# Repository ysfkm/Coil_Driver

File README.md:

# Coil Driver

## Summary
- Board hosting three independent bi-directional coil drivers (up to 3A each) off a shared +15V supply, using an H-bridge per channel for direction control.
- Setpoints for each channel's analog current control loop are set digitally over a backplane bus (address + data bits → DAC → analog loop); 4-layer 163mm x 100mm PCB.

## Specs
- **Input:** Digital Bus from backplane
  - A0~A7 as addresses
  - D9~D14 as data bits
- **Supply:** An external +15V with 10A rating and +15V from backplane
- **Output:** three bi-directional current up to 3A
- **Description:** Three separate coil drivers each capable of outputting 3A using the same +15V supply to output current. Utilizes digital interface from the backplane to set the setpoints for the analog current control loops separately and uses H-bridge to achieve bi-directional capability.
- **PCB:** 163mm x 100mm / 4 Layer

> **⚠ Note:** When setting a setpoint via the SPI lines, make sure the DIR bits are all driven to the right value since all DIR bits would be updated at the same time, not just the targeted channel for setpoint adjustment.

> **⚠ Note:** For the jumper selecting +15V power supply, make sure either ALL FOUR middle pins are connected or the LEFT AND RIGHT pins are connected, NEVER BOTH.

## Voltage / Nets

| Voltage / Nets | Purpose |
|---|---|
| +15V_EXT | External supply for driving large currents |
| +15V_BP | Backplane supply for regulating voltages and driving small currents |
| +15V | Jumper implemented to choose between +15V_EXT and +15V_BP<br>Drives main op-amp for current output<br>Drives MOSFETs to control H-bridge switching |
| +6V | Regulated from +15_BP, used to regulate +5VA |
| +5VA | Drives DAC and sensing op-amp. Used to generate VREF for DAC |
| +5V | Backplane supply to regulate +3V3 |
| +3V3 | Backplane supply for digital decoder |
| +3V3A | Regulated from +15V_BP, drives DAC |

## Modules

### Root page
- Backplane connector with digital bus, supply, and ground
- This board's own address switch
- Digital decoder latching the data bits when address from A0~A7 matches

### Power Supply page
- Several ferrite beads to connect different ground domains

### DAC
- Takes the three SPI lines and output 0~3V setpoint
- Has four channels, three used for each analog control loop
- Own regulator to precisely generate reference voltage (3V)

### Analog Control pages
All three are basically identical and have the following:
- Main op-amp driving the current
- Setpoint at main op-amp
- Compensator at main op-amp
- Current sense feedback network and voltage amplifier
- H-bridge
- MOSFET gate driver that drives the H-bridge based on DIR bit

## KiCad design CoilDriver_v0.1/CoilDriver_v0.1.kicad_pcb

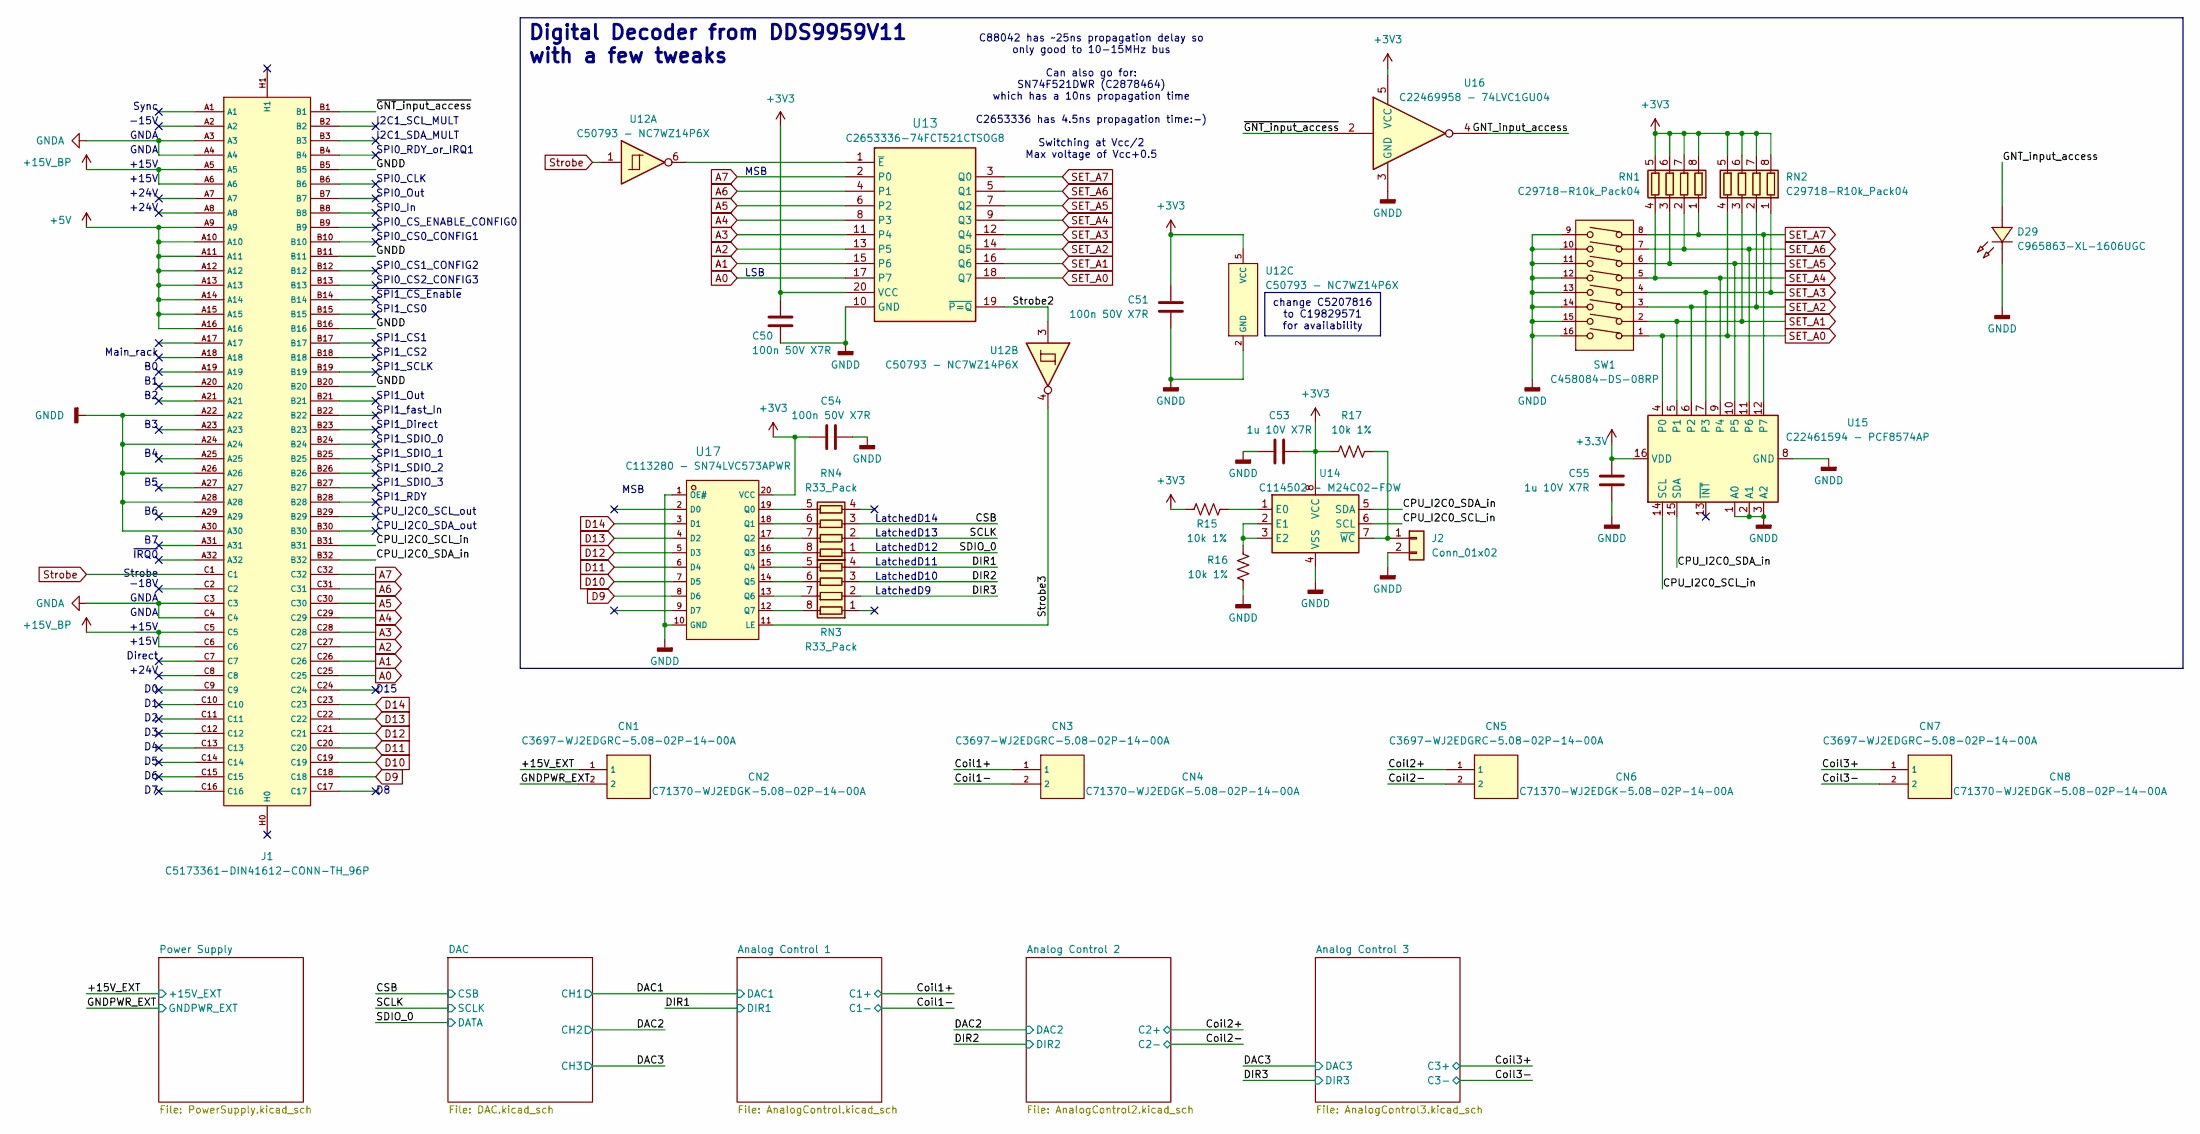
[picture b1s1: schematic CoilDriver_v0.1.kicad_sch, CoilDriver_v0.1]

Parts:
C50, C51, C54: 100n 50V X7R; C_0402_1005Metric; LCSC C307331
C53, C55: 1u 10V X7R; C_0402_1005Metric; LCSC C7500381
CN1, CN3, CN5, CN7: C3697-WJ2EDGRC-5.08-02P-14-00A; C3697-CONN-TH_2P-P5.08_WJ2EDGRC-5.08-2P; LCSC C3697
CN2, CN4, CN6, CN8: C71370-WJ2EDGK-5.08-02P-14-00A; C71370-FL_001; LCSC C71370
D29: C965863-XL-1606UGC; C965863-LED-SMD_L1.7-W1.1-R-RD_ORANGE; LCSC C965863
J1: C5173361-DIN41612-CONN-TH_96P; C5173361-DIN41612-96P; LCSC C5173361
J2: Conn_01x02; C492401-HDR-TH_2P-P2.54-V-M; LCSC C492401
R15, R16, R17: 10k 1%; R_0402_1005Metric; LCSC C2906861
RN1, RN2: C29718-R10k_Pack04; C29718-RES-ARRAY-SMD_0603-8P-L3.2-W1.6-BL; LCSC C29718
RN3, RN4: R33_Pack; C25508-RES-ARRAY-SMD_0603-8P-L3.2-W1.6-BL; LCSC C25508
SW1: C458084-DS-08RP; C458084-SW-TH_DS-08RP; LCSC C458084
U12: C50793 - NC7WZ14P6X; C50793-SC-70-6_L2.2-W1.3-P0.65-LS2.2-BR; LCSC C50793
U13: C2653336-74FCT521CTSOG8; C2653336-SOIC127P1032X265-20N; LCSC C2653336
U14: C114502 - M24C02-FDW; C114502-SOIC-8_L4.9-W3.9-P1.27-LS6.0-BL; LCSC C114502
U15: C22461594 - PCF8574AP; C22461594-TSSOP-16_L5.0-W4.4-P0.65-LS6.4-BL-1; LCSC C22461594
U16: C22469958 - 74LVC1GU04; C22469958-SOT-353-5_L2.1-W1.3-P0.65-LS2.3-BL; LCSC C22469958
U17: C113280 - SN74LVC573APWR; C113280-TSSOP-20_L6.5-W4.4-P0.65-LS6.4-BL; LCSC C113280

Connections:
+3.3V: C55.1, U15.16 (VDD)
+3V3: C50.1, C51.1, C53.1, C54.1, R15.1, R17.1, RN1.5 (R4.2), RN1.6 (R3.2), RN1.7 (R2.2), RN1.8 (R1.2), RN2.5 (R4.2), RN2.6 (R3.2), RN2.7 (R2.2), RN2.8 (R1.2), U12.5 (VCC), U13.20 (VCC), U14.8 (VCC), U16.5 (VCC), U17.20 (VCC); also elsewhere on the board
+5V: J1.A9, J1.A10, J1.A11, J1.A12, J1.A13, J1.A14, J1.A15, J1.A16; also elsewhere on the board
+15V_BP: J1.A5, J1.A6, J1.C5, J1.C6; also elsewhere on the board
/+15V_EXT: CN1.1; also elsewhere on the board
/CPU_I2C0_SCL_in: J1.B31, U14.6 (SCL), U15.14 (SCL)
/CPU_I2C0_SDA_in: J1.B32, U14.5 (SDA), U15.15 (SDA)
/CSB: RN4.3 (R3.1); also elsewhere on the board
/Coil1+: CN3.1; also elsewhere on the board
/Coil1-: CN3.2; also elsewhere on the board
/Coil2+: CN5.1; also elsewhere on the board
/Coil2-: CN5.2; also elsewhere on the board
/Coil3+: CN7.1; also elsewhere on the board
/Coil3-: CN7.2; also elsewhere on the board
/DIR1: RN3.4 (R4.1); also elsewhere on the board
/DIR2: RN3.3 (R3.1); also elsewhere on the board
/DIR3: RN3.2 (R2.1); also elsewhere on the board
/GNT_input_access: D29.2 (A), U16.4
/SCLK: RN4.2 (R2.1); also elsewhere on the board
/SDIO_0: RN4.1 (R1.1); also elsewhere on the board
/Strobe2: U12.3, U13.19 (~P=Q)
/Strobe3: U12.4, U17.11 (LE)
/~GNT_input_access: J1.B1, U16.2
A0: J1.C25, U13.17 (P7)
A1: J1.C26, U13.15 (P6)
A2: J1.C27, U13.13 (P5)
A3: J1.C28, U13.11 (P4)
A4: J1.C29, U13.8 (P3)
A5: J1.C30, U13.6 (P2)
A6: J1.C31, U13.4 (P1)
A7: J1.C32, U13.2 (P0)
D9: J1.C18, U17.8 (D6)
D10: J1.C19, U17.7 (D5)
D11: J1.C20, U17.6 (D4)
D12: J1.C21, U17.5 (D3)
D13: J1.C22, U17.4 (D2)
D14: J1.C23, U17.3 (D1)
GNDA: J1.A3, J1.A4, J1.C3, J1.C4; also elsewhere on the board
GNDD: C50.2, C51.2, C53.2, C54.2, C55.2, D29.1 (K), J1.A22, J1.A24, J1.A26, J1.A28, J1.A30, J1.B5, J1.B11, J1.B16, J1.B20, J2.2, R16.2, SW1.9, SW1.10, SW1.11, SW1.12, SW1.13, SW1.14, SW1.15, SW1.16, U12.2 (GND), U13.10 (GND), U14.4 (VSS), U15.1 (A0), U15.2 (A1), U15.3 (A2), U15.8 (GND), U16.3 (GND), U17.1 (OE#), U17.10 (GND); also elsewhere on the board
GNDPWR: CN1.2; also elsewhere on the board
unnamed: J2.1, R17.2, U14.7 (~WC)
unnamed: RN3.8 (R1.2), U17.12 (Q7)
unnamed: RN3.7 (R2.2), U17.13 (Q6)
unnamed: RN3.6 (R3.2), U17.14 (Q5)
unnamed: RN3.5 (R4.2), U17.15 (Q4)
unnamed: RN4.8 (R1.2), U17.16 (Q3)
unnamed: RN4.7 (R2.2), U17.17 (Q2)
unnamed: RN4.6 (R3.2), U17.18 (Q1)
unnamed: RN4.5 (R4.2), U17.19 (Q0)
unnamed: U12.6, U13.1 (~E)
unnamed: R15.2, U14.1 (E0)
unnamed: R16.1, U14.2 (E1), U14.3 (E2)
SET_A0: RN2.4 (R4.1), SW1.1, U13.18 (Q7), U15.4 (P0)
SET_A1: RN2.3 (R3.1), SW1.2, U13.16 (Q6), U15.5 (P1)
SET_A2: RN2.2 (R2.1), SW1.3, U13.14 (Q5), U15.6 (P2)
SET_A3: RN2.1 (R1.1), SW1.4, U13.12 (Q4), U15.7 (P3)
SET_A4: RN1.4 (R4.1), SW1.5, U13.9 (Q3), U15.9 (P4)
SET_A5: RN1.3 (R3.1), SW1.6, U13.7 (Q2), U15.10 (P5)
SET_A6: RN1.2 (R2.1), SW1.7, U13.5 (Q1), U15.11 (P6)
SET_A7: RN1.1 (R1.1), SW1.8, U13.3 (Q0), U15.12 (P7)
Strobe: J1.C1, U12.1

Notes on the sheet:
Main_rack
CPU_I2C0_SCL_out
SPI1_Direct
SPI0_CS2_CONFIG3
+24V
SPI0_CS_ENABLE_CONFIG0
+15V
SPI0_In
LatchedD14
Strobe
SPI1_CS1
SPI1_SCLK
SPI1_SDIO_2
SPI1_SDIO_3
SPI1_Out
Direct
GNDA
-18V
SPI1_SDIO_1
LatchedD11
CPU_I2C0_SDA_out
MSB
Sync
~{IRQ0}
LatchedD9
SPI0_CLK
D15
SPI0_Out
LSB
LatchedD10
SPI0_CS1_CONFIG2
SPI1_CS0
LatchedD13
SPI1_CS2
~{SPI1_CS_Enable}
SPI0_RDY_or_IRQ1
C88042 has ~25ns propagation delay so only good to 10-15MHz bus Can also go for: SN74F521DWR (C2878464) which has a 10ns propagation time C2653336 has 4.5ns propagation time:-) Switching at Vcc/2 Max voltage of Vcc+0.5
I2C1_SCL_MULT
I2C1_SDA_MULT
SPI1_SDIO_0

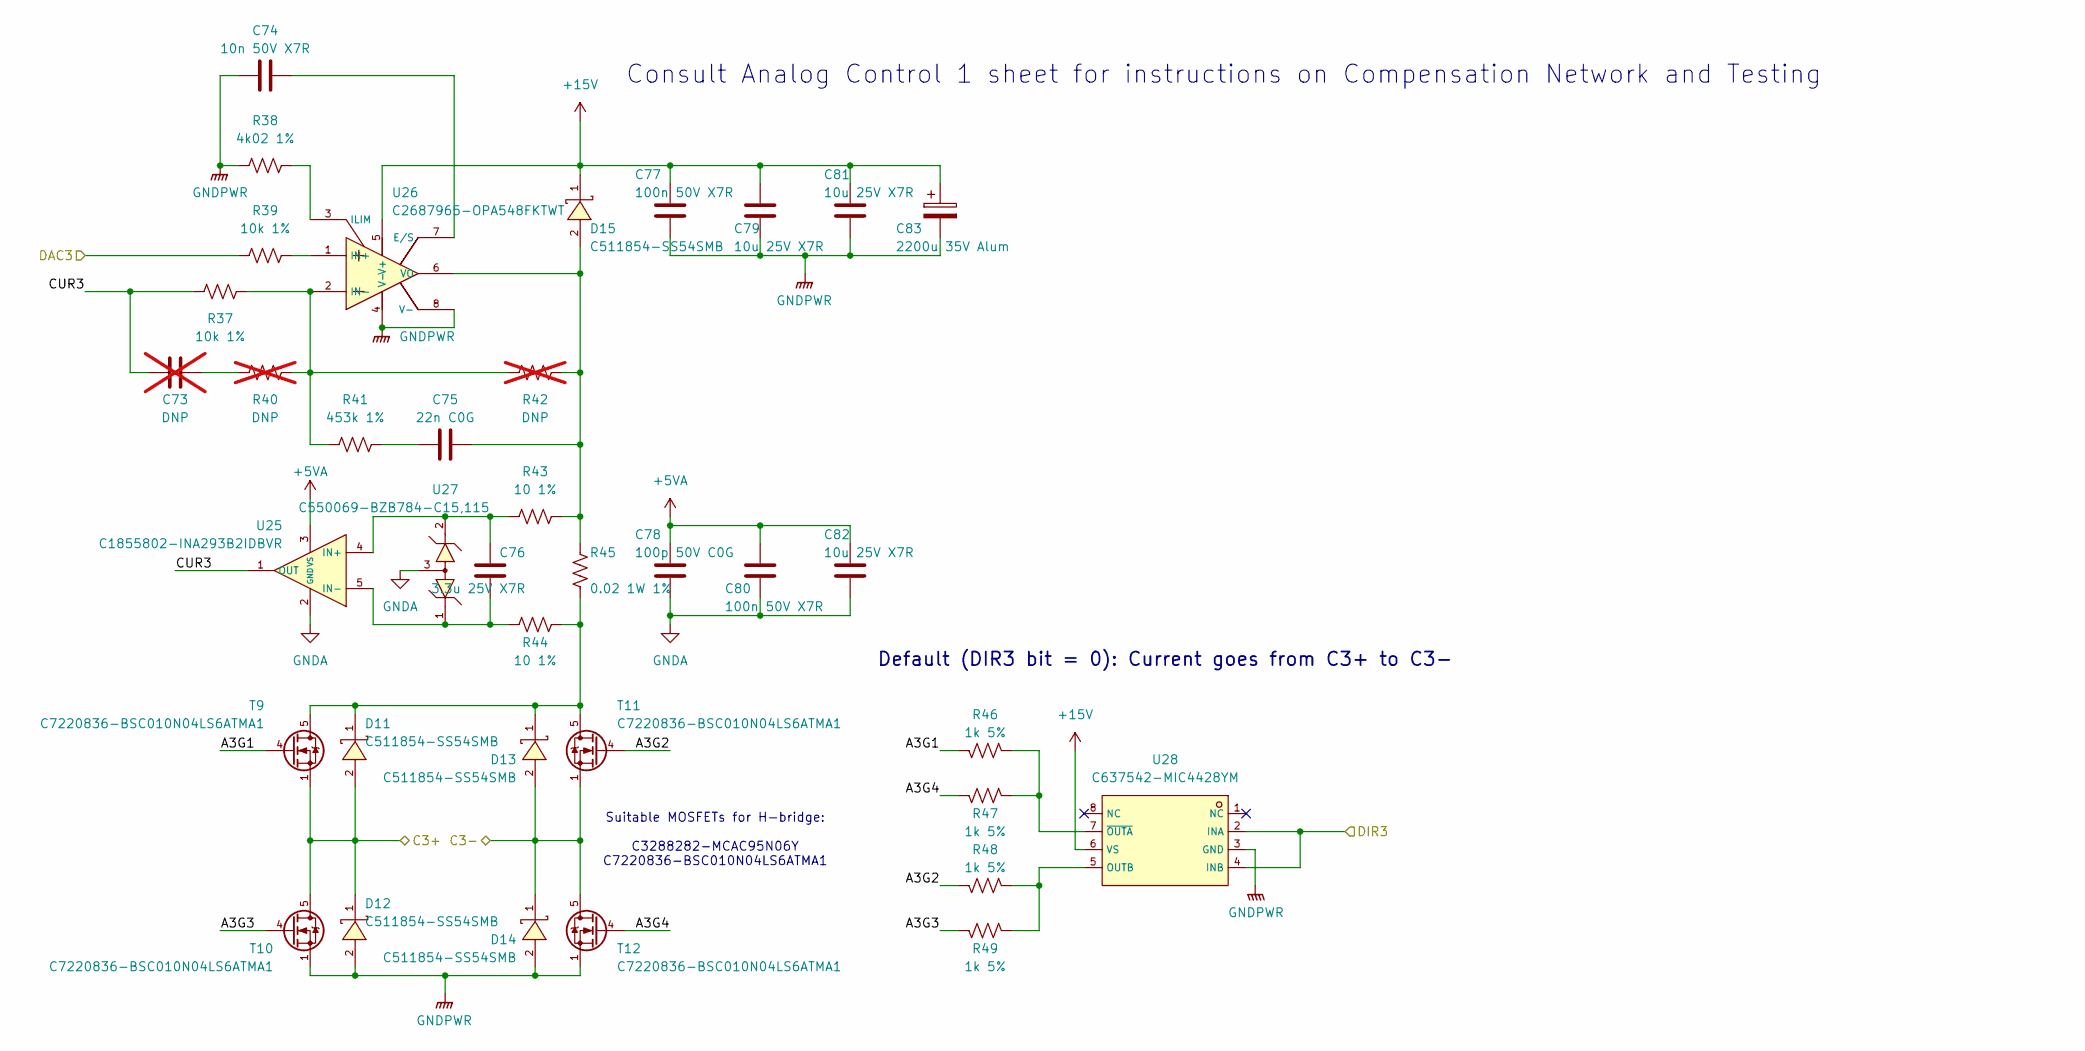
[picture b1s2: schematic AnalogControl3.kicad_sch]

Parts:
C73: DNP; C_0805_2012Metric; not fitted
C74: 10n 50V X7R; C_0402_1005Metric; LCSC C15195
C75: 22n C0G; C_0805_2012Metric; LCSC C2181592
C76: 3.3u 25V X7R; C_0805_2012Metric; LCSC C7393948
C77, C80: 100n 50V X7R; C_0402_1005Metric; LCSC C307331
C78: 100p 50V C0G; C_0402_1005Metric; LCSC C1546
C79, C81, C82: 10u 25V X7R; C_0805_2012Metric; LCSC C3039694
C83: 2200u 35V Alum; C3829879-CAP-SMD_BD16.0-L17.0-W17.0-LS18.0-FD; LCSC C3829879
D11, D12, D13, D14, D15: C511854-SS54SMB; C511854-SMB_L4.6-W3.6-LS5.3-RD; LCSC C511854
R37, R39: 10k 1%; R_0402_1005Metric; LCSC C2906861
R38: 4k02 1%; R_0402_1005Metric; LCSC C324800
R40, R42: DNP; R_0603_1608Metric; not fitted
R41: 453k 1%; R_0402_1005Metric; LCSC C3013172
R43, R44: 10 1%; R_0402_1005Metric; LCSC C138066
R45: 0.02 1W 1%; R_1206_3216Metric; LCSC C7420010
R46, R47, R48, R49: 1k 5%; R_0402_1005Metric; LCSC C2906899
T9, T10, T11, T12: C7220836-BSC010N04LS6ATMA1; C7220836-TDSON-8_L6.0-W5.0-P1.27-LS6.2-BL_1; LCSC C7220836
U25: C1855802-INA293B2IDBVR; C1855802-SOT-23-5_L2.9-W1.6-P0.95-LS2.8-BR; LCSC C1855802
U26: C2687965-OPA548FKTWT; C2687965-TO-263-7_L10.2-W8.9-P1.27-LS15.2-BL; LCSC C2687965
U27: C550069-BZB784-C15,115; C550069-SOT-323-3_L2.0-W1.3-P1.30-LS2.1-BR; LCSC C550069
U28: C637542-MIC4428YM; C637542-SOIC-8_L4.9-W3.9-P1.27-LS6.0-BL; LCSC C637542

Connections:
+5VA: C78.1, C80.1, C82.1, U25.3 (VS); also elsewhere on the board
+15V: C77.1, C79.1, C81.1, C83.1, D15.1 (K), U26.5 (V+), U28.6 (VS); also elsewhere on the board
/Analog Control 3/A3G1: R46.2, T9.4 (G)
/Analog Control 3/A3G2: R48.2, T11.4 (G)
/Analog Control 3/A3G3: R49.2, T10.4 (G)
/Analog Control 3/A3G4: R47.2, T12.4 (G)
/Analog Control 3/CUR3: C73.1, R37.1, U25.1 (OUT)
/Coil3+: D11.2 (A), D12.1 (K), T9.1 (S), T10.5 (D); also elsewhere on the board
/Coil3-: D13.2 (A), D14.1 (K), T11.1 (S), T12.5 (D); also elsewhere on the board
/DAC3: R39.1; also elsewhere on the board
/DIR3: U28.2 (INA), U28.4 (INB); also elsewhere on the board
GNDA: C78.2, C80.2, C82.2, U25.2 (GND), U27.3; also elsewhere on the board
GNDPWR: C74.1, C77.2, C79.2, C81.2, C83.2, D12.2 (A), D14.2 (A), R38.1, T10.1 (S), T12.1 (S), U26.4 (V-), U26.8 (V-), U28.3 (GND); also elsewhere on the board
unnamed: C73.2, R40.1
unnamed: C75.1, R41.2
unnamed: D11.1 (K), D13.1 (K), R44.1, R45.1, T9.5 (D), T11.5 (D)
unnamed: C75.2, D15.2 (A), R42.2, R43.1, R45.2, U26.6 (VO)
unnamed: C76.2, R43.2, U25.4 (IN+), U27.2
unnamed: C76.1, R44.2, U25.5 (IN-), U27.1
unnamed: C74.2, U26.7 (E/S)
unnamed: R38.2, U26.3 (ILIM)
unnamed: R39.2, U26.1 (IN+)
unnamed: R37.2, R40.2, R41.1, R42.1, U26.2 (IN-)
unnamed: R48.1, R49.1, U28.5 (OUTB)
unnamed: R46.1, R47.1, U28.7 (~OUTA)

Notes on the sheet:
Consult Analog Control 1 sheet for instructions on Compensation Network and Testing
Default (DIR3 bit = 0): Current goes from C3+ to C3-
Suitable MOSFETs for H-bridge: C3288282-MCAC95N06Y C7220836-BSC010N04LS6ATMA1

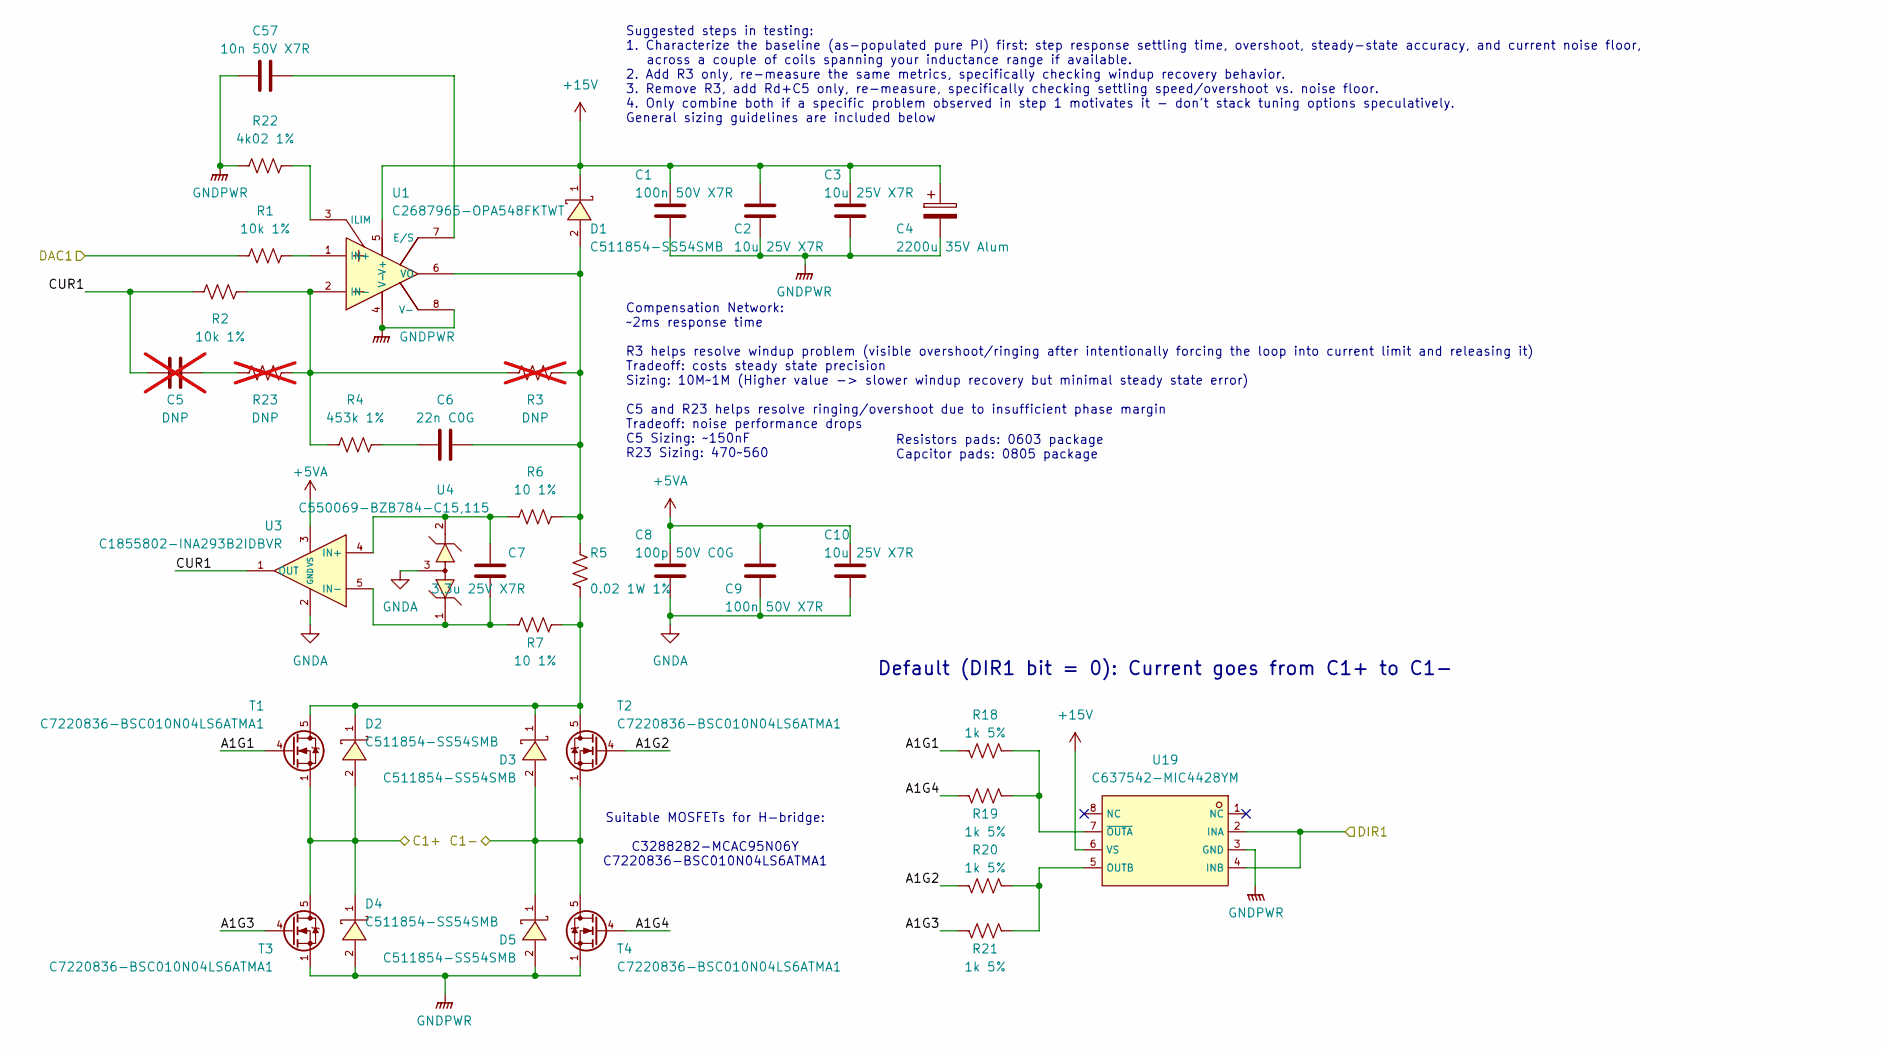
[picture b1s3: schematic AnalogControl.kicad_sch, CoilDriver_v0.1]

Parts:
C1, C9: 100n 50V X7R; C_0402_1005Metric; LCSC C307331
C2, C3, C10: 10u 25V X7R; C_0805_2012Metric; LCSC C3039694
C4: 2200u 35V Alum; C3829879-CAP-SMD_BD16.0-L17.0-W17.0-LS18.0-FD; LCSC C3829879
C5: DNP; C_0805_2012Metric; not fitted
C6: 22n C0G; C_0805_2012Metric; LCSC C2181592
C7: 3.3u 25V X7R; C_0805_2012Metric; LCSC C7393948
C8: 100p 50V C0G; C_0402_1005Metric; LCSC C1546
C57: 10n 50V X7R; C_0402_1005Metric; LCSC C15195
D1, D2, D3, D4, D5: C511854-SS54SMB; C511854-SMB_L4.6-W3.6-LS5.3-RD; LCSC C511854
R1, R2: 10k 1%; R_0402_1005Metric; LCSC C2906861
R3, R23: DNP; R_0603_1608Metric; not fitted
R4: 453k 1%; R_0402_1005Metric; LCSC C3013172
R5: 0.02 1W 1%; R_1206_3216Metric; LCSC C7420010
R6, R7: 10 1%; R_0402_1005Metric; LCSC C138066
R18, R19, R20, R21: 1k 5%; R_0402_1005Metric; LCSC C2906899
R22: 4k02 1%; R_0402_1005Metric; LCSC C324800
T1, T2, T3, T4: C7220836-BSC010N04LS6ATMA1; C7220836-TDSON-8_L6.0-W5.0-P1.27-LS6.2-BL_1; LCSC C7220836
U1: C2687965-OPA548FKTWT; C2687965-TO-263-7_L10.2-W8.9-P1.27-LS15.2-BL; LCSC C2687965
U3: C1855802-INA293B2IDBVR; C1855802-SOT-23-5_L2.9-W1.6-P0.95-LS2.8-BR; LCSC C1855802
U4: C550069-BZB784-C15,115; C550069-SOT-323-3_L2.0-W1.3-P1.30-LS2.1-BR; LCSC C550069
U19: C637542-MIC4428YM; C637542-SOIC-8_L4.9-W3.9-P1.27-LS6.0-BL; LCSC C637542

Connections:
+5VA: C8.1, C9.1, C10.1, U3.3 (VS); also elsewhere on the board
+15V: C1.1, C2.1, C3.1, C4.1, D1.1 (K), U1.5 (V+), U19.6 (VS); also elsewhere on the board
/Analog Control 1/A1G1: R18.2, T1.4 (G)
/Analog Control 1/A1G2: R20.2, T2.4 (G)
/Analog Control 1/A1G3: R21.2, T3.4 (G)
/Analog Control 1/A1G4: R19.2, T4.4 (G)
/Analog Control 1/CUR1: C5.1, R2.1, U3.1 (OUT)
/Coil1+: D2.2 (A), D4.1 (K), T1.1 (S), T3.5 (D); also elsewhere on the board
/Coil1-: D3.2 (A), D5.1 (K), T2.1 (S), T4.5 (D); also elsewhere on the board
/DAC1: R1.1; also elsewhere on the board
/DIR1: U19.2 (INA), U19.4 (INB); also elsewhere on the board
GNDA: C8.2, C9.2, C10.2, U3.2 (GND), U4.3; also elsewhere on the board
GNDPWR: C1.2, C2.2, C3.2, C4.2, C57.1, D4.2 (A), D5.2 (A), R22.1, T3.1 (S), T4.1 (S), U1.4 (V-), U1.8 (V-), U19.3 (GND); also elsewhere on the board
unnamed: C5.2, R23.1
unnamed: C6.1, R4.2
unnamed: C6.2, D1.2 (A), R3.2, R5.2, R6.1, U1.6 (VO)
unnamed: D2.1 (K), D3.1 (K), R5.1, R7.1, T1.5 (D), T2.5 (D)
unnamed: C57.2, U1.7 (E/S)
unnamed: R22.2, U1.3 (ILIM)
unnamed: R1.2, U1.1 (IN+)
unnamed: R2.2, R3.1, R4.1, R23.2, U1.2 (IN-)
unnamed: C7.2, R6.2, U3.4 (IN+), U4.2
unnamed: C7.1, R7.2, U3.5 (IN-), U4.1
unnamed: R20.1, R21.1, U19.5 (OUTB)
unnamed: R18.1, R19.1, U19.7 (~OUTA)

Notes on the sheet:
Default (DIR1 bit = 0): Current goes from C1+ to C1-
Suitable MOSFETs for H-bridge: C3288282-MCAC95N06Y C7220836-BSC010N04LS6ATMA1
Suggested steps in testing: 1. Characterize the baseline (as-populated pure PI) first: step response settling time, overshoot, steady-state accuracy, and current noise floor, across a couple of coils spanning your inductance range if available. 2. Add R3 only, re-measure the same metrics, specifica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
Compensation Network: ~2ms response time R3 helps resolve windup problem (visible overshoot/ringing after intentionally forcing the loop into current limit and releasing it) Tradeoff: costs steady state precision Sizing: 10M~1M (Higher value -> slower windup recovery but minimal steady state error)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
Resistors pads: 0603 package Capcitor pads: 0805 package

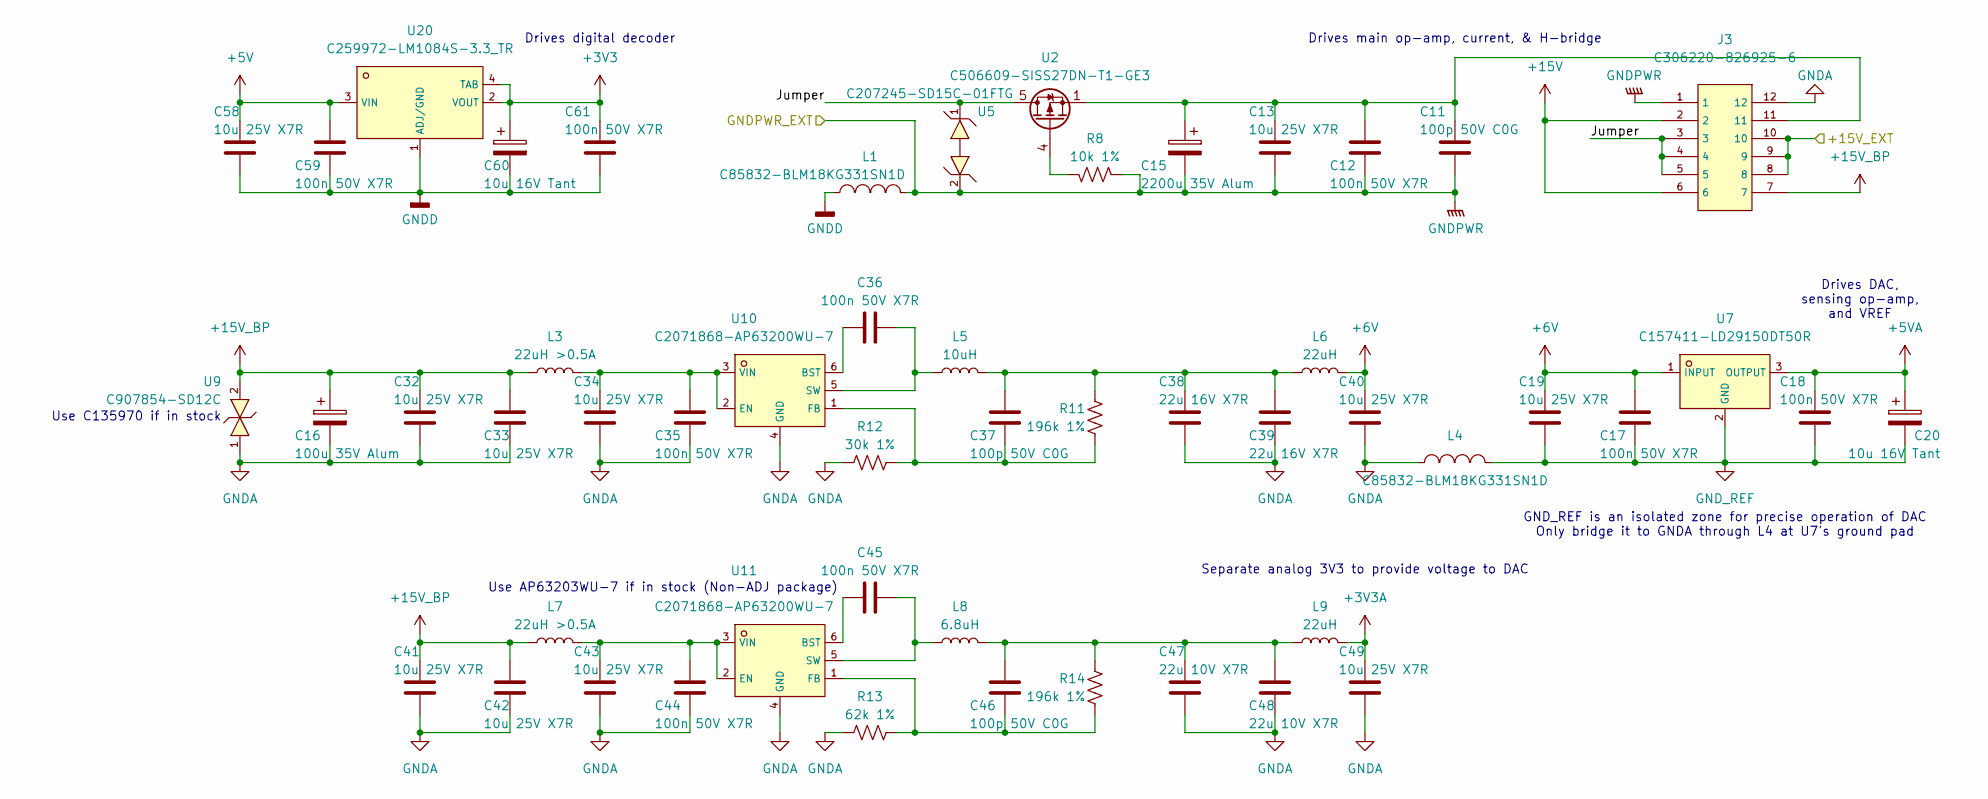
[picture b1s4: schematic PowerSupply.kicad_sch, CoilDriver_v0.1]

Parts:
C11, C37, C46: 100p 50V C0G; C_0402_1005Metric; LCSC C1546
C12, C17, C18, C35, C36, C44, C45, C59, C61: 100n 50V X7R; C_0402_1005Metric; LCSC C307331
C13, C19, C32, C33, C34, C40, C41, C42, C43, C49, C58: 10u 25V X7R; C_0805_2012Metric; LCSC C3039694
C15: 2200u 35V Alum; C3829879-CAP-SMD_BD16.0-L17.0-W17.0-LS18.0-FD; LCSC C3829879
C16: 100u 35V Alum; C2887272-CAP-SMD_BD6.3-L6.6-W6.6-LS7.2-FD_3; LCSC C2887272
C20, C60: 10u 16V Tant; C119051-CASE-A_3216; LCSC C119051
C38, C39: 22u 16V X7R; C_1206_3216Metric; LCSC C7472972
C47, C48: 22u 10V X7R; C_0805_2012Metric; LCSC C907991
J3: C306220-826925-6; C306220-CONN-TH_12P-P2.54_826925-6; LCSC C306220
L1, L4: C85832-BLM18KG331SN1D; C85832-L0603; LCSC C85832
L3, L7: 22uH >0.5A; L_1812_4532Metric; LCSC C22469096
L5: 10uH; C540965-IND-SMD_L6.5-W6.5_VISHAY; LCSC C540965
L6, L9: 22uH; C842901-IND-SMD_L7.0-W6.6; LCSC C842901
L8: 6.8uH; C177249-IND-SMD_L5.4-W5.2_FXL0530; LCSC C177249
R8: 10k 1%; R_0402_1005Metric; LCSC C2906861
R11, R14: 196k 1%; R_0402_1005Metric; LCSC C3013157
R12: 30k 1%; R_0402_1005Metric; LCSC C2909347
R13: 62k 1%; R_0402_1005Metric; LCSC C2909375
U2: C506609-SISS27DN-T1-GE3; C506609-POWERPAK-1212-8_L3.3-W3.3-P0.65-BL-EP; LCSC C506609
U5: C207245-SD15C-01FTG; C207245-SOD-323_L1.7-W1.3-LS2.5-BI-1; LCSC C207245
U7: C157411-LD29150DT50R; C157411-TO-252-3_L6.5-W5.8-P4.58-BL; LCSC C157411
U9: C907854-SD12C; C907854-SOD-323_L1.7-W1.3-LS2.5-BI; LCSC C907854
U10, U11: C2071868-AP63200WU-7; C2071868-SOT-23-6_L2.9-W1.6-P0.95-LS2.8-BR; LCSC C2071868
U20: C259972-LM1084S-3.3_TR; C259972-TO-263-3_L8.6-W10.2-P2.54-LS14.4-TL; LCSC C259972

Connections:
+3V3: C60.1, C61.1, U20.2 (VOUT), U20.4 (TAB); also elsewhere on the board
+3V3A: C49.1, L9.2; also elsewhere on the board
+5V: C58.1, C59.1, U20.3 (VIN); also elsewhere on the board
+5VA: C18.1, C20.1, U7.3 (OUTPUT); also elsewhere on the board
+6V: C17.1, C19.1, C40.1, L6.2, U7.1 (INPUT)
+15V: J3.2, J3.6; also elsewhere on the board
+15V_BP: C16.1, C32.1, C33.1, C41.1, C42.1, J3.7, L3.1, L7.1, U9.2; also elsewhere on the board
/+15V_EXT: J3.8, J3.9, J3.10; also elsewhere on the board
/Power Supply/Jumper: J3.3, J3.4, J3.5, U2.5 (D), U2.6 (D), U2.7 (D), U2.8 (D), U2.9 (D), U5.1
GNDA: C16.2, C32.2, C33.2, C34.2, C35.2, C38.2, C39.2, C40.2, C41.2, C42.2, C43.2, C44.2, C47.2, C48.2, C49.2, J3.12, L4.1, R12.1, R13.1, U9.1, U10.4 (GND), U11.4 (GND); also elsewhere on the board
GNDD: C58.2, C59.2, C60.2, C61.2, L1.2, U20.1 (ADJ/GND); also elsewhere on the board
GNDPWR: C11.2, C12.2, C13.2, C15.2, J3.1, L1.1, R8.1, U5.2; also elsewhere on the board
GND_REF: C17.2, C18.2, C19.2, C20.2, L4.2, U7.2 (GND); also elsewhere on the board
unnamed: C11.1, C12.1, C13.1, C15.1, J3.11, U2.1 (S), U2.2 (S), U2.3 (S)
unnamed: C37.1, C38.1, C39.1, L5.2, L6.1, R11.2
unnamed: C46.1, C47.1, C48.1, L8.2, L9.1, R14.2
unnamed: R8.2, U2.4 (G)
unnamed: C36.1, U10.6 (BST)
unnamed: C34.1, C35.1, L3.2, U10.2 (EN), U10.3 (VIN)
unnamed: C37.2, R11.1, R12.2, U10.1 (FB)
unnamed: C36.2, L5.1, U10.5 (SW)
unnamed: C45.1, U11.6 (BST)
unnamed: C43.1, C44.1, L7.2, U11.2 (EN), U11.3 (VIN)
unnamed: C46.2, R13.2, R14.1, U11.1 (FB)
unnamed: C45.2, L8.1, U11.5 (SW)

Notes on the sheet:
Drives digital decoder
Drives main op-amp, current, & H-bridge
Drives DAC, sensing op-amp, and VREF
GND_REF is an isolated zone for precise operation of DAC Only bridge it to GNDA through L4 at U7's ground pad
Use C135970 if in stock
Separate analog 3V3 to provide voltage to DAC
Use AP63203WU-7 if in stock (Non-ADJ package)

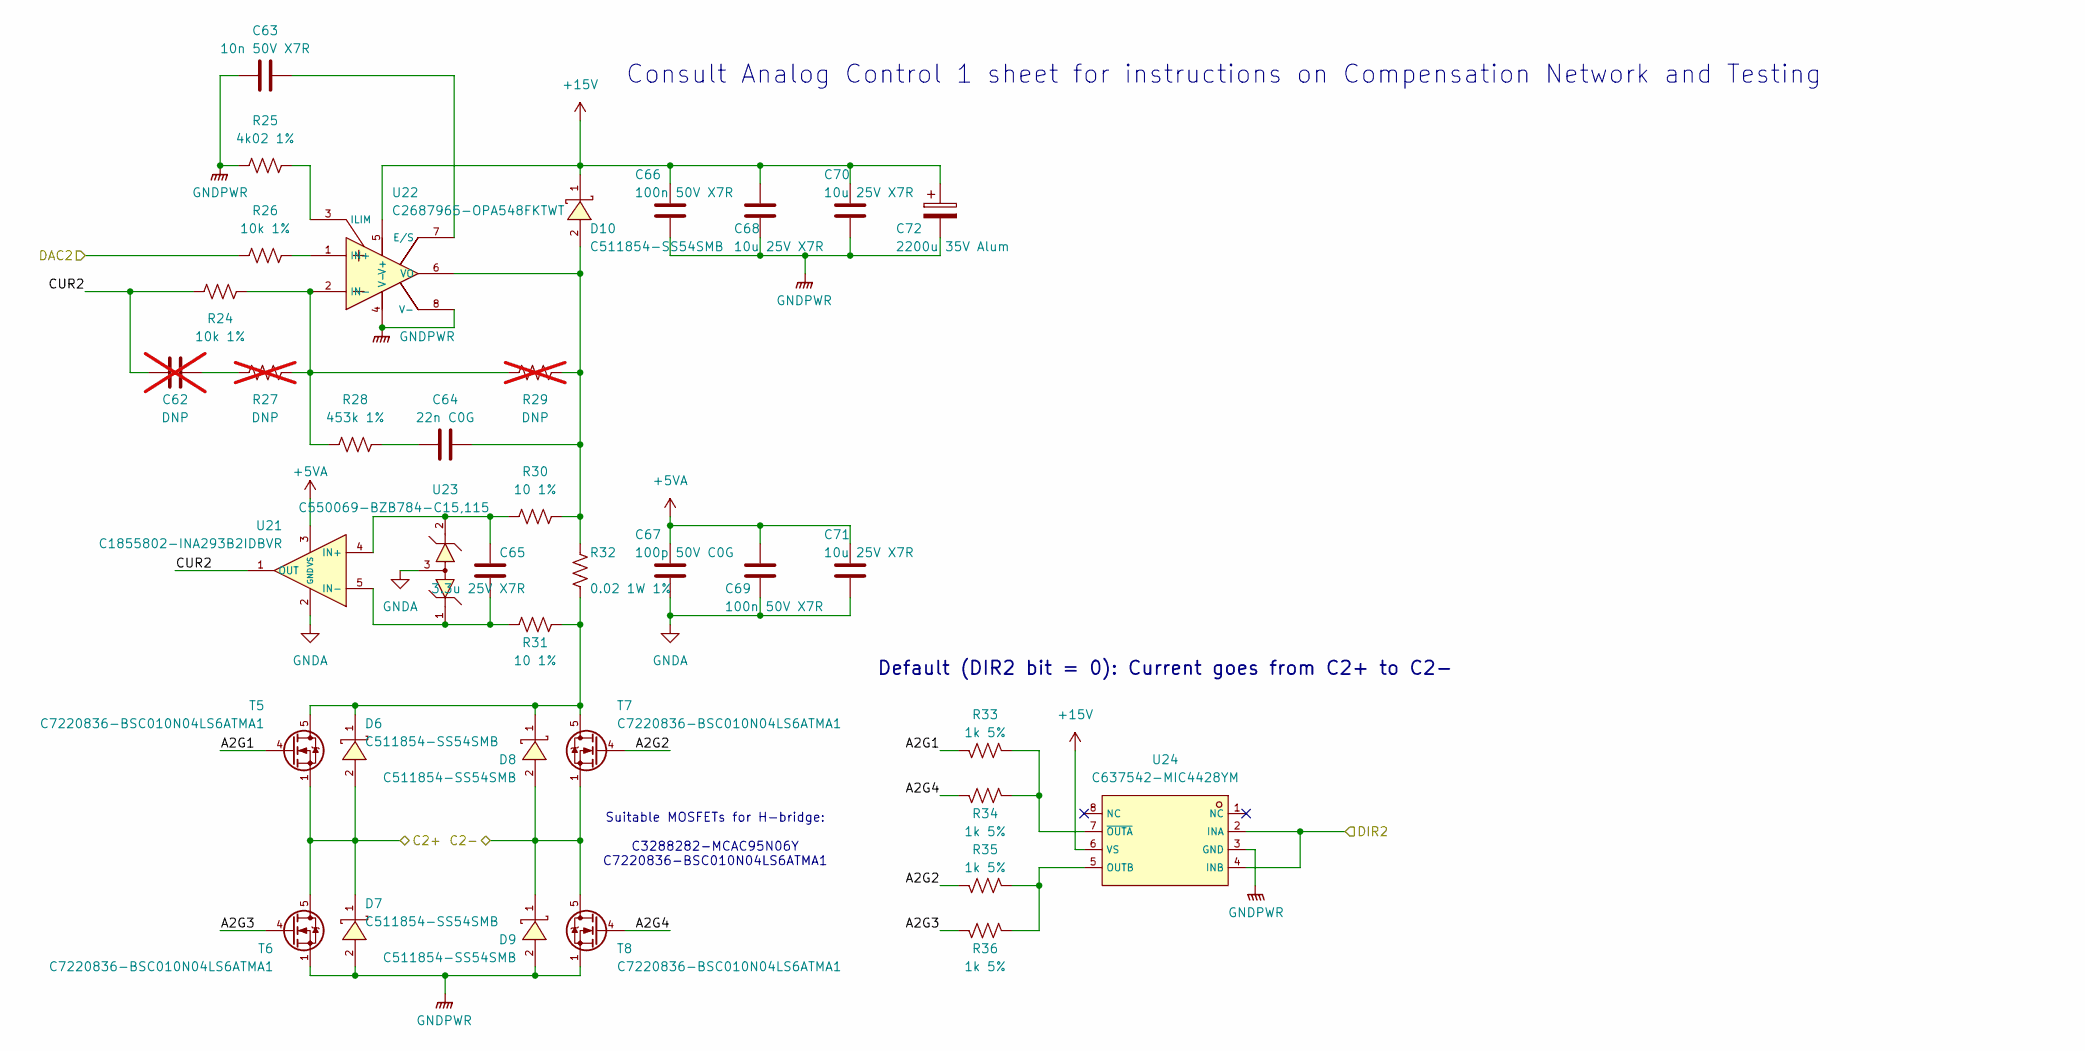
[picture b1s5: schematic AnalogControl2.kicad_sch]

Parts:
C62: DNP; C_0805_2012Metric; not fitted
C63: 10n 50V X7R; C_0402_1005Metric; LCSC C15195
C64: 22n C0G; C_0805_2012Metric; LCSC C2181592
C65: 3.3u 25V X7R; C_0805_2012Metric; LCSC C7393948
C66, C69: 100n 50V X7R; C_0402_1005Metric; LCSC C307331
C67: 100p 50V C0G; C_0402_1005Metric; LCSC C1546
C68, C70, C71: 10u 25V X7R; C_0805_2012Metric; LCSC C3039694
C72: 2200u 35V Alum; C3829879-CAP-SMD_BD16.0-L17.0-W17.0-LS18.0-FD; LCSC C3829879
D6, D7, D8, D9, D10: C511854-SS54SMB; C511854-SMB_L4.6-W3.6-LS5.3-RD; LCSC C511854
R24, R26: 10k 1%; R_0402_1005Metric; LCSC C2906861
R25: 4k02 1%; R_0402_1005Metric; LCSC C324800
R27, R29: DNP; R_0603_1608Metric; not fitted
R28: 453k 1%; R_0402_1005Metric; LCSC C3013172
R30, R31: 10 1%; R_0402_1005Metric; LCSC C138066
R32: 0.02 1W 1%; R_1206_3216Metric; LCSC C7420010
R33, R34, R35, R36: 1k 5%; R_0402_1005Metric; LCSC C2906899
T5, T6, T7, T8: C7220836-BSC010N04LS6ATMA1; C7220836-TDSON-8_L6.0-W5.0-P1.27-LS6.2-BL_1; LCSC C7220836
U21: C1855802-INA293B2IDBVR; C1855802-SOT-23-5_L2.9-W1.6-P0.95-LS2.8-BR; LCSC C1855802
U22: C2687965-OPA548FKTWT; C2687965-TO-263-7_L10.2-W8.9-P1.27-LS15.2-BL; LCSC C2687965
U23: C550069-BZB784-C15,115; C550069-SOT-323-3_L2.0-W1.3-P1.30-LS2.1-BR; LCSC C550069
U24: C637542-MIC4428YM; C637542-SOIC-8_L4.9-W3.9-P1.27-LS6.0-BL; LCSC C637542

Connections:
+5VA: C67.1, C69.1, C71.1, U21.3 (VS); also elsewhere on the board
+15V: C66.1, C68.1, C70.1, C72.1, D10.1 (K), U22.5 (V+), U24.6 (VS); also elsewhere on the board
/Analog Control 2/A2G1: R33.2, T5.4 (G)
/Analog Control 2/A2G2: R35.2, T7.4 (G)
/Analog Control 2/A2G3: R36.2, T6.4 (G)
/Analog Control 2/A2G4: R34.2, T8.4 (G)
/Analog Control 2/CUR2: C62.1, R24.1, U21.1 (OUT)
/Coil2+: D6.2 (A), D7.1 (K), T5.1 (S), T6.5 (D); also elsewhere on the board
/Coil2-: D8.2 (A), D9.1 (K), T7.1 (S), T8.5 (D); also elsewhere on the board
/DAC2: R26.1; also elsewhere on the board
/DIR2: U24.2 (INA), U24.4 (INB); also elsewhere on the board
GNDA: C67.2, C69.2, C71.2, U21.2 (GND), U23.3; also elsewhere on the board
GNDPWR: C63.1, C66.2, C68.2, C70.2, C72.2, D7.2 (A), D9.2 (A), R25.1, T6.1 (S), T8.1 (S), U22.4 (V-), U22.8 (V-), U24.3 (GND); also elsewhere on the board
unnamed: C62.2, R27.1
unnamed: C64.1, R28.2
unnamed: D6.1 (K), D8.1 (K), R31.1, R32.1, T5.5 (D), T7.5 (D)
unnamed: C64.2, D10.2 (A), R29.2, R30.1, R32.2, U22.6 (VO)
unnamed: C65.2, R30.2, U21.4 (IN+), U23.2
unnamed: C65.1, R31.2, U21.5 (IN-), U23.1
unnamed: C63.2, U22.7 (E/S)
unnamed: R25.2, U22.3 (ILIM)
unnamed: R26.2, U22.1 (IN+)
unnamed: R24.2, R27.2, R28.1, R29.1, U22.2 (IN-)
unnamed: R35.1, R36.1, U24.5 (OUTB)
unnamed: R33.1, R34.1, U24.7 (~OUTA)

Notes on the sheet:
Default (DIR2 bit = 0): Current goes from C2+ to C2-
Suitable MOSFETs for H-bridge: C3288282-MCAC95N06Y C7220836-BSC010N04LS6ATMA1
Consult Analog Control 1 sheet for instructions on Compensation Network and Testing
